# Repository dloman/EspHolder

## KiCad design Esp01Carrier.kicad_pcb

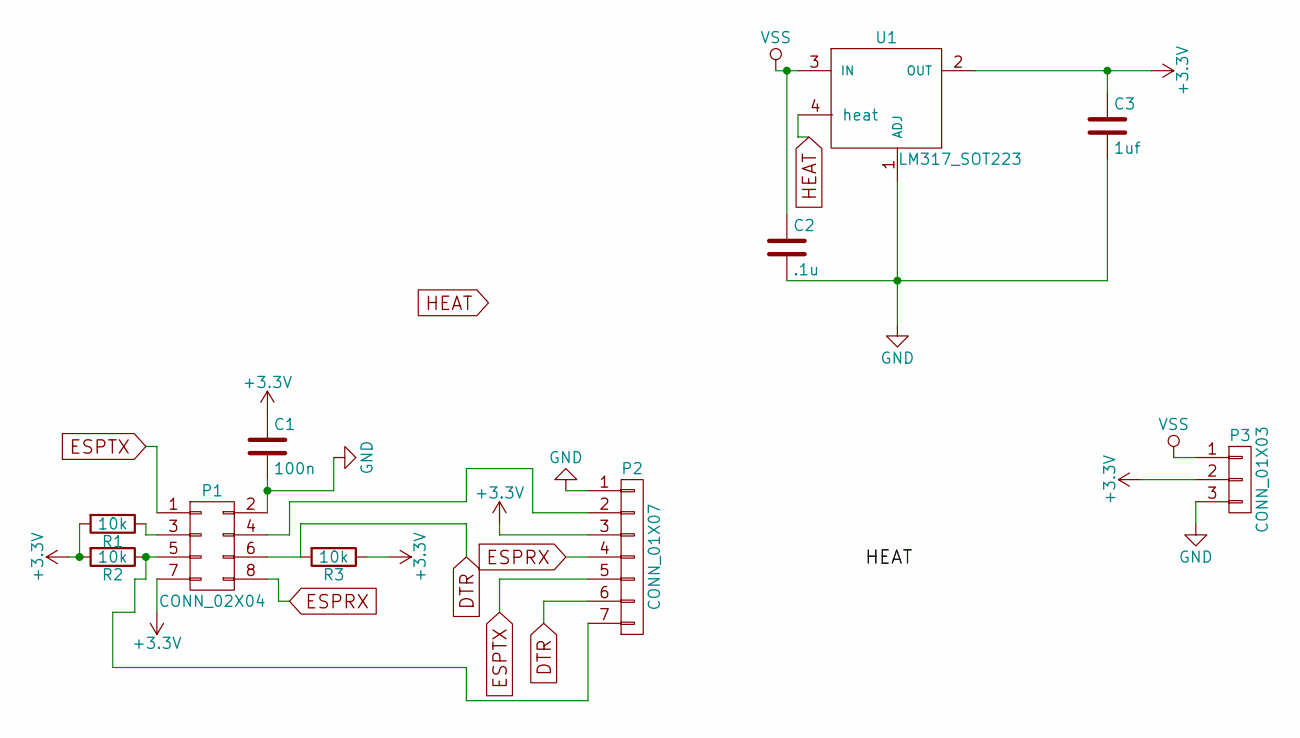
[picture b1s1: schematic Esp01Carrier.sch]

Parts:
C1: 100n; C_0805_HandSoldering
C2: .1u; C_0805_HandSoldering
C3: 1uf; C_0805_HandSoldering
P1: CONN_02X04; Pin_Header_Straight_2x04
P2: CONN_01X07; Pin_Header_Straight_1x07
P3: CONN_01X03; TerminalBlock_Pheonix_MKDS1.5-3pol
R1, R2, R3: 10k; R_0805_HandSoldering
U1: LM317_SOT223; SOT-223

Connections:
+3V3: C1.1, C3.1, P1.7, P2.3, P3.2, R1.2, R2.2, R3.1, U1.2 (OUT)
DTR: P1.6, P2.6, R3.2
ESPRX: P1.8, P2.4
ESPTX: P1.1, P2.5
GND: C1.2, C2.2, C3.2, P1.2, P2.1, P3.3, U1.1 (ADJ)
HEAT: U1.4 (heat)
unnamed: P1.3, R1.1
unnamed: P1.4, P2.2
unnamed: P1.5, P2.7, R2.1
VSS: C2.1, P3.1, U1.3 (IN)

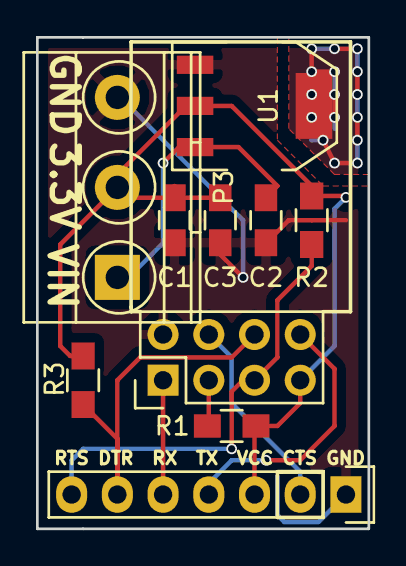
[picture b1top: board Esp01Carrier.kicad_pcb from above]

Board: 2 copper layers, 18.4 x 27.3 mm, 10 parts (0 on the bottom side), 9 nets.

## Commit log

2016-04-14 initial commit of version 2
2016-04-30 updated to version III
